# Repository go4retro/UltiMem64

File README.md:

# UltiMem64 

A 2 IC SRAM replacement for the Commodore 64 that offers all of the advantages of the VSP-fixed 64kB SRAM modules plus 2 megabytes of directly accessible RAM using a full featured memory management unit (MMU).

## Introduction

UltiMem64 replace the 2 4464 DRAM ICs on newer Commodore 64 motherboards (and can be installed in older 8-IC 4164 DRAM based motherboards using the DRAMCarrier PCB) and provides access to 2 megabytes of direct memory access (not REU access). The memory is instantly available when requested, no DMA needed.  The Color RAM IC installs in the 2114 space on motherboards containing a 2114 Color RAM and provides access to 64 kilobytes of Color memory nybbles.

## Technical Details

(*Although this information is currently correct, it may change based on developer feedback*)

The Commodore 64 64kB address space is partitioned into 16 4kB "pages", corresponding to the first nybble of a 16 bit address (the 'D' in $D0FF). The 2MB SRAM is likewise also partitioned into 4kB pages, which can then be mapped into any (or all) of the 16 slots in the MMU.

The MMU also supports the concept of a "mapping set", which means the developer can arrange up to 256 different 16 slot memory mappings, and choose any one of them at will.  Swapping out 64kB of RAM can take as little as 4 cycles (sta MAPPING_REG).

The system starts up in "hidden" mode, where the registers cannot be set or read from memory.  Reading some "magic addresses" will unhide the registers:

- $C0AA
- $C055
- $C0FF
- $C000
- $CO&lt;PAGE&gt;, where &lt;page&gt; is the high byte of the location where the registers should appear ($FF would place the registers at $ff00-)

Once the registers are visible, the are as follows:

| Register           | Bit  | Note                                       |
| ------------------ | ---- | ------------------------------------------ |
| BASE               | 0    | MMU enabled                                |
| BASE+1             | 7:0  | MMU mapping "window"                       |
| BASE+2             | 7:0  | MMU mapping in use                         |
| BASE+3             | 6:0  | Color RAM 1kB mapping                      |
| BASE+10 to BASE+1F | 7:0  | Low bits of 16 MMU mappings (16 mappings)  |
| BASE+20 to BASE+2F | 7:0  | High bits of 16 MMU mappings (16 mappings) |

To map memory, set the mapping "window" to the set you wish to change, and then alter the data in values BASE+10 to BASE+2F.  To run the code in that mapping, set the value of the map usage register to the desired map number (0-255).

Currently, to hide the registers, simply read the magic memory locations again and set the <page> to be 0.

The MMU replaces the upper 4 bits of the 16 bit memory address with the 9 bits of data from the mapping registers, using the upper 4 bits as a 0-15 "index" into the mapping set (mapping 0 will be used for memory access in the $0XXX range, etc.).  When the MMU is off, only the first 64kB of the SRAM is visible.

Since any mapping can point to any 4kB space in the real address space, one can place the same memory bank in multiple locations in the address map (map $123C00 so it appears at $4C00 and $FC00) or other interesting combinations.

The Color RAM mapping is simpler, and is simply a 6 bit value that choose which of the 64 1kB Color RAM "pages" will be used for the Color RAM data. There is no way to set Color RAM without switching to that specific mapping, so it is best to populate/change Color RAM during video blanking periods.

## Future Directions:

- Expand SRAM to 8MB (Alliance offers an 8MB SRAM in the same footprint)
- Utilize top two bits of MMU mapping to set read/write and IRQ on write flags for any 5kB page.
- Support a way to set mapping set without unhiding all registers (like 128 does)
- Possibly support a way to support auto-incremented memory store/read.

## License
Copyright (C) 2019-20  RETRO Innovations

These files are free designs; you can redistribute them and/or modify
them under the terms of the Creative Commons Attribution-ShareAlike 
4.0 International License.

You should have received a copy of the license along with this
work. If not, see <http://creativecommons.org/licenses/by-sa/4.0/>.

These files are distributed in the hope that they will be useful,
but WITHOUT ANY WARRANTY; without even the implied warranty of
MERCHANTABILITY or FITNESS FOR A PARTICULAR PURPOSE.  See the
license for more details.

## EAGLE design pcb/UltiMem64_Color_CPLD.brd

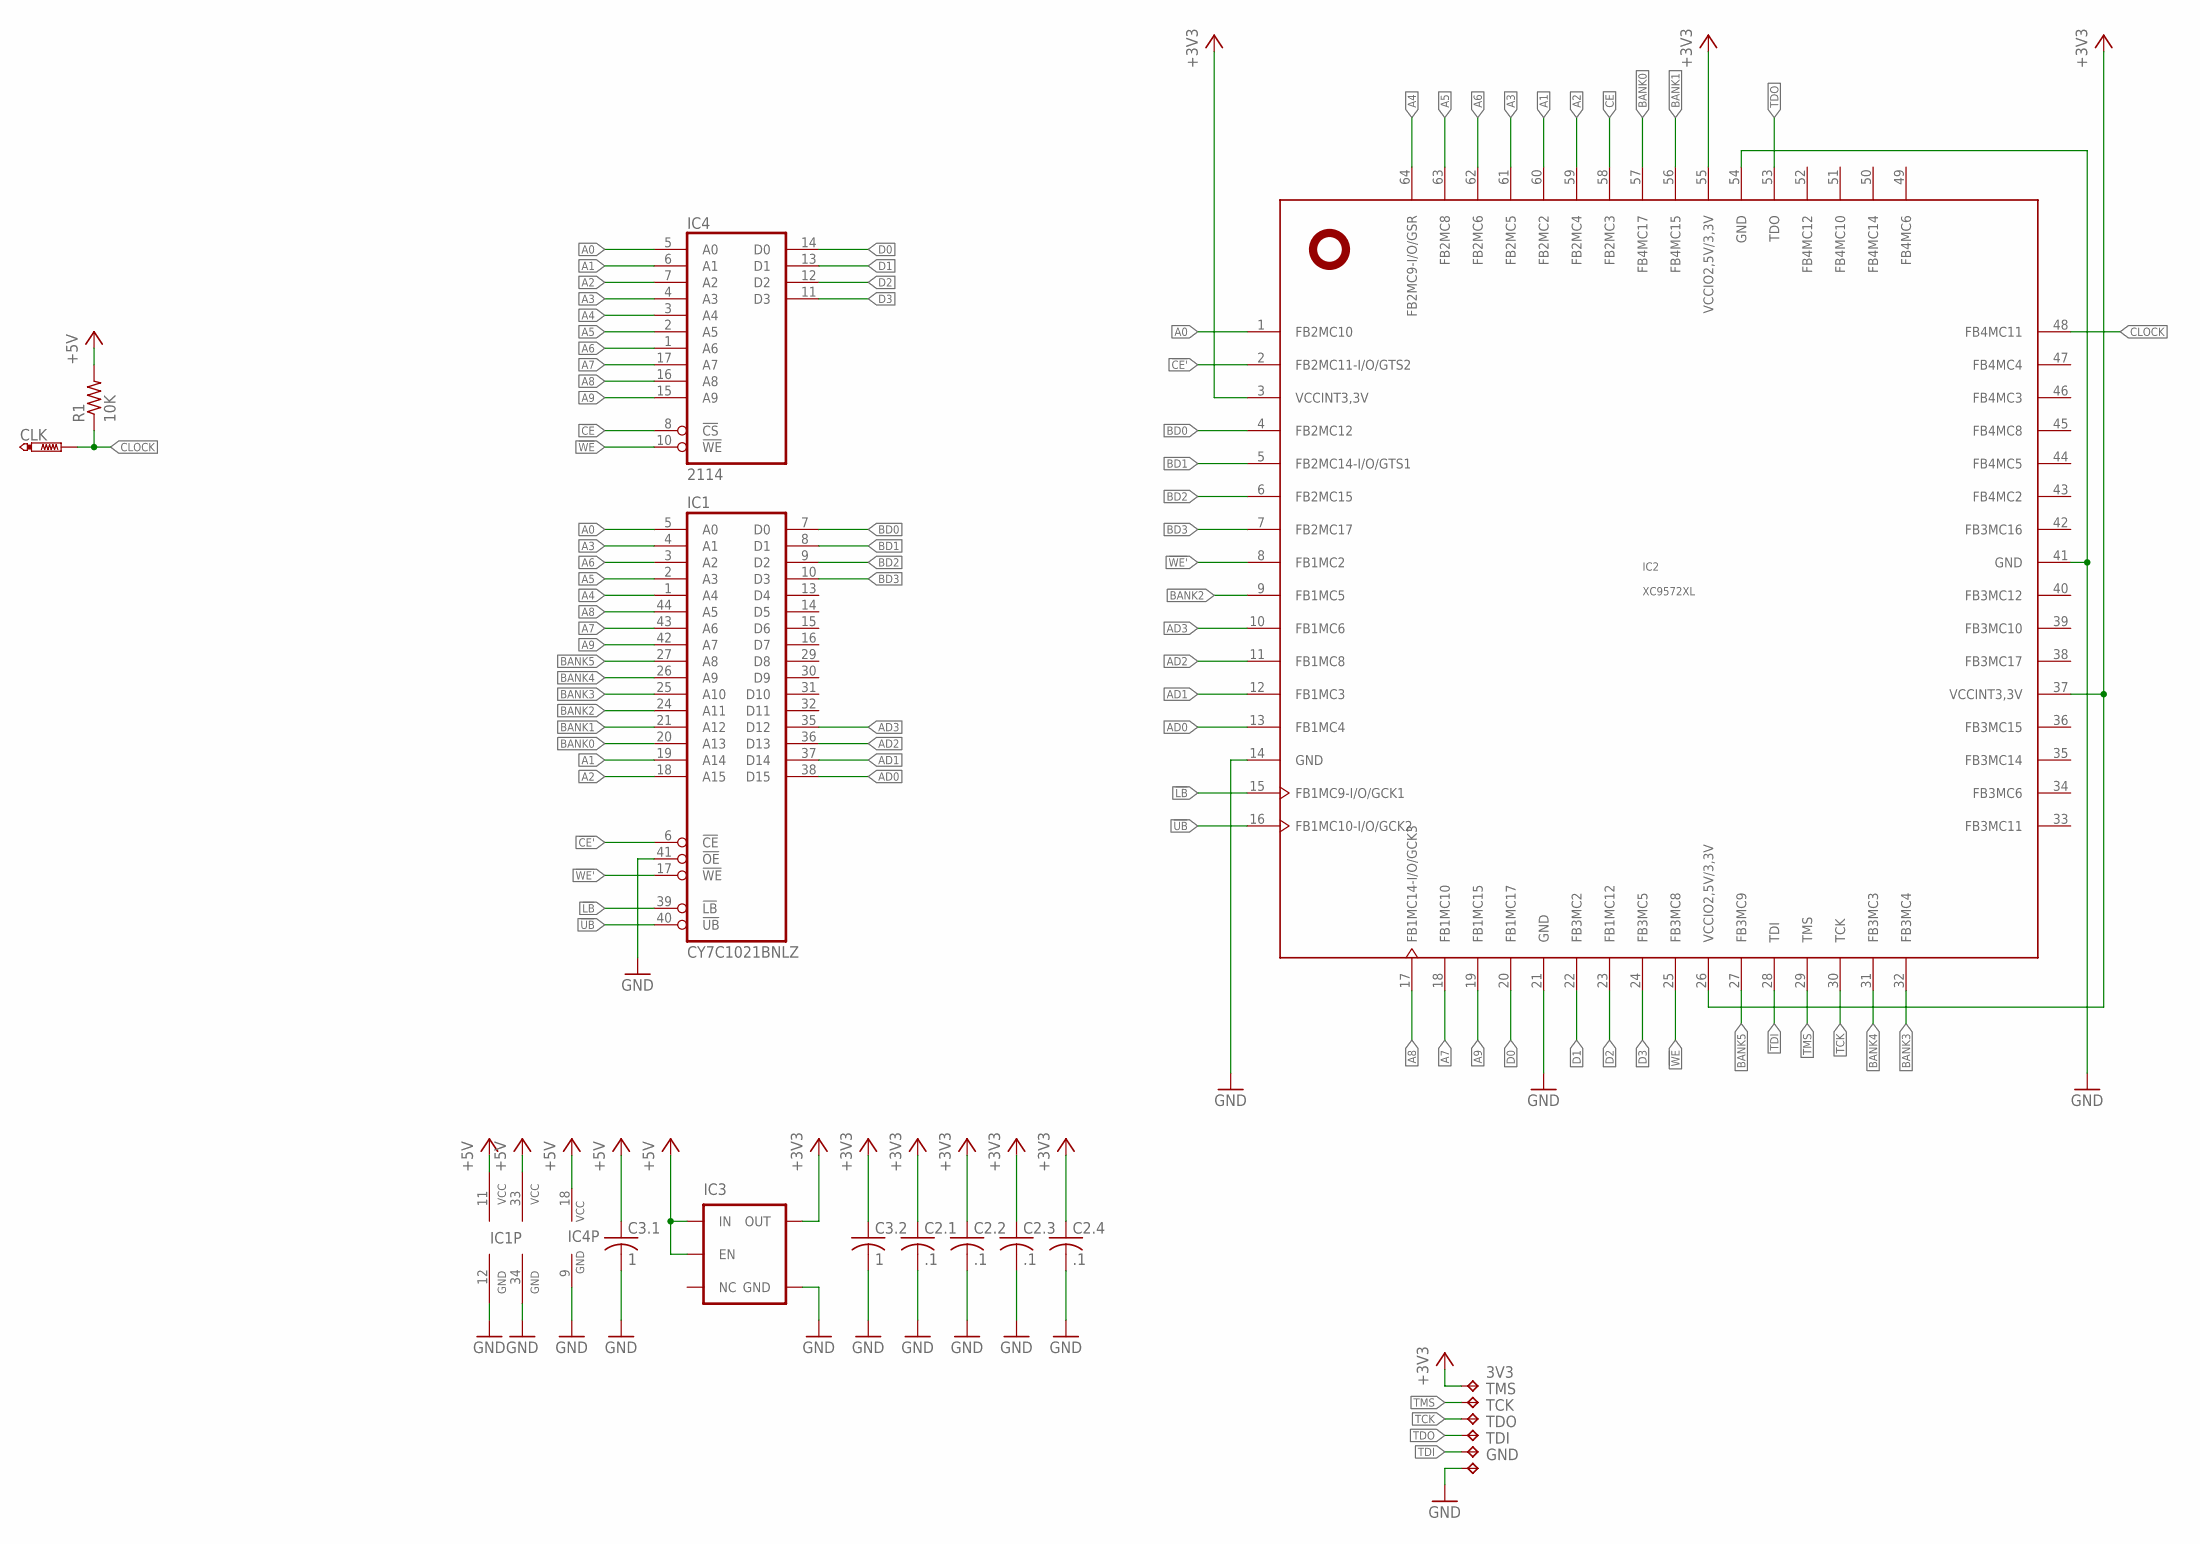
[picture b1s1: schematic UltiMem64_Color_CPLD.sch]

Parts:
3V3: TPTP09R; TP09R
C2.1, C2.2, C2.3, C2.4: .1; C0402
C3.1, C3.2: 1; C0402
CLK: PTR1PAD1-13; P1-13
GND: TPTP09R; TP09R
IC1: CY7C1021BNLZ; TSOP44-II
IC2: XC9572XL; VQFP64
IC3: V_REG_TPS76433SOT23-5; SOT23-5
IC4: 2114; DIL18-SMD-REVERSE
R1: 10K; R0402
TCK: TPTP09R; TP09R
TDI: TPTP09R; TP09R
TDO: TPTP09R; TP09R
TMS: TPTP09R; TP09R

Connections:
!CE: IC2.58 (FB2MC3), IC4.8 (!CS)
!CE': IC1.6 (!CE), IC2.2 (FB2MC11-I/O/GTS2)
!LB: IC1.39 (!LB), IC2.15 (FB1MC9-I/O/GCK1)
!UB: IC1.40 (!UB), IC2.16 (FB1MC10-I/O/GCK2)
!WE: IC2.25 (FB3MC8), IC4.10 (!WE)
!WE': IC1.17 (!WE), IC2.8 (FB1MC2)
+3V3: 3V3.TP, C2.1.1, C2.2.1, C2.3.1, C2.4.1, C3.2.1, IC2.3 (VCCINT3,3V), IC2.26 (VCCIO2,5V/3,3V), IC2.37 (VCCINT3,3V), IC2.55 (VCCIO2,5V/3,3V), IC3.5 (OUT)
+5V: C3.1.1, IC1.11 (VCC), IC1.33 (VCC), IC3.1 (IN), IC3.3 (EN), IC4.18 (VCC), R1.2
A0: IC1.5 (A0), IC2.1 (FB2MC10), IC4.5 (A0)
A1: IC1.19 (A14), IC2.60 (FB2MC2), IC4.6 (A1)
A2: IC1.18 (A15), IC2.59 (FB2MC4), IC4.7 (A2)
A3: IC1.4 (A1), IC2.61 (FB2MC5), IC4.4 (A3)
A4: IC1.1 (A4), IC2.64 (FB2MC9-I/O/GSR), IC4.3 (A4)
A5: IC1.2 (A3), IC2.63 (FB2MC8), IC4.2 (A5)
A6: IC1.3 (A2), IC2.62 (FB2MC6), IC4.1 (A6)
A7: IC1.43 (A6), IC2.18 (FB1MC10), IC4.17 (A7)
A8: IC1.44 (A5), IC2.17 (FB1MC14-I/O/GCK3), IC4.16 (A8)
A9: IC1.42 (A7), IC2.19 (FB1MC15), IC4.15 (A9)
AD0: IC1.38 (D15), IC2.13 (FB1MC4)
AD1: IC1.37 (D14), IC2.12 (FB1MC3)
AD2: IC1.36 (D13), IC2.11 (FB1MC8)
AD3: IC1.35 (D12), IC2.10 (FB1MC6)
BANK0: IC1.20 (A13), IC2.57 (FB4MC17)
BANK1: IC1.21 (A12), IC2.56 (FB4MC15)
BANK2: IC1.24 (A11), IC2.9 (FB1MC5)
BANK3: IC1.25 (A10), IC2.32 (FB3MC4)
BANK4: IC1.26 (A9), IC2.31 (FB3MC3)
BANK5: IC1.27 (A8), IC2.27 (FB3MC9)
BD0: IC1.7 (D0), IC2.4 (FB2MC12)
BD1: IC1.8 (D1), IC2.5 (FB2MC14-I/O/GTS1)
BD2: IC1.9 (D2), IC2.6 (FB2MC15)
BD3: IC1.10 (D3), IC2.7 (FB2MC17)
CLOCK: CLK.TP, IC2.48 (FB4MC11), R1.1
D0: IC2.20 (FB1MC17), IC4.14 (D0)
D1: IC2.22 (FB3MC2), IC4.13 (D1)
D2: IC2.23 (FB1MC12), IC4.12 (D2)
D3: IC2.24 (FB3MC5), IC4.11 (D3)
GND: C2.1.2, C2.2.2, C2.3.2, C2.4.2, C3.1.2, C3.2.2, GND.TP, IC1.12 (GND), IC1.34 (GND), IC1.41 (!OE), IC2.14 (GND), IC2.21 (GND), IC2.41 (GND), IC2.54 (GND), IC3.2 (GND), IC4.9 (GND)
TCK: IC2.30 (TCK), TCK.TP
TDI: IC2.28 (TDI), TDI.TP
TDO: IC2.53 (TDO), TDO.TP
TMS: IC2.29 (TMS), TMS.TP

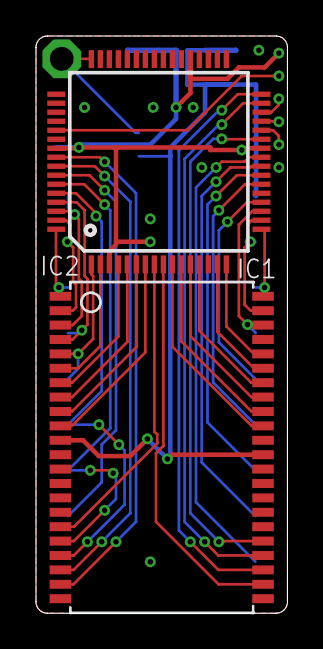
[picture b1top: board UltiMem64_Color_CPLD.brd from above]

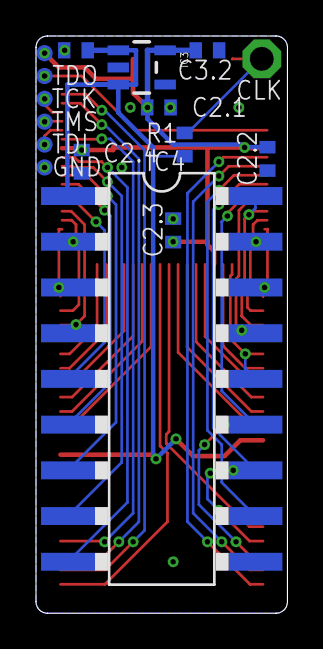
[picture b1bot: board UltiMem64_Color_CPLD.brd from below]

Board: 2 copper layers, 14.0 x 32.1 mm, 18 parts (15 on the bottom side), 42 nets.

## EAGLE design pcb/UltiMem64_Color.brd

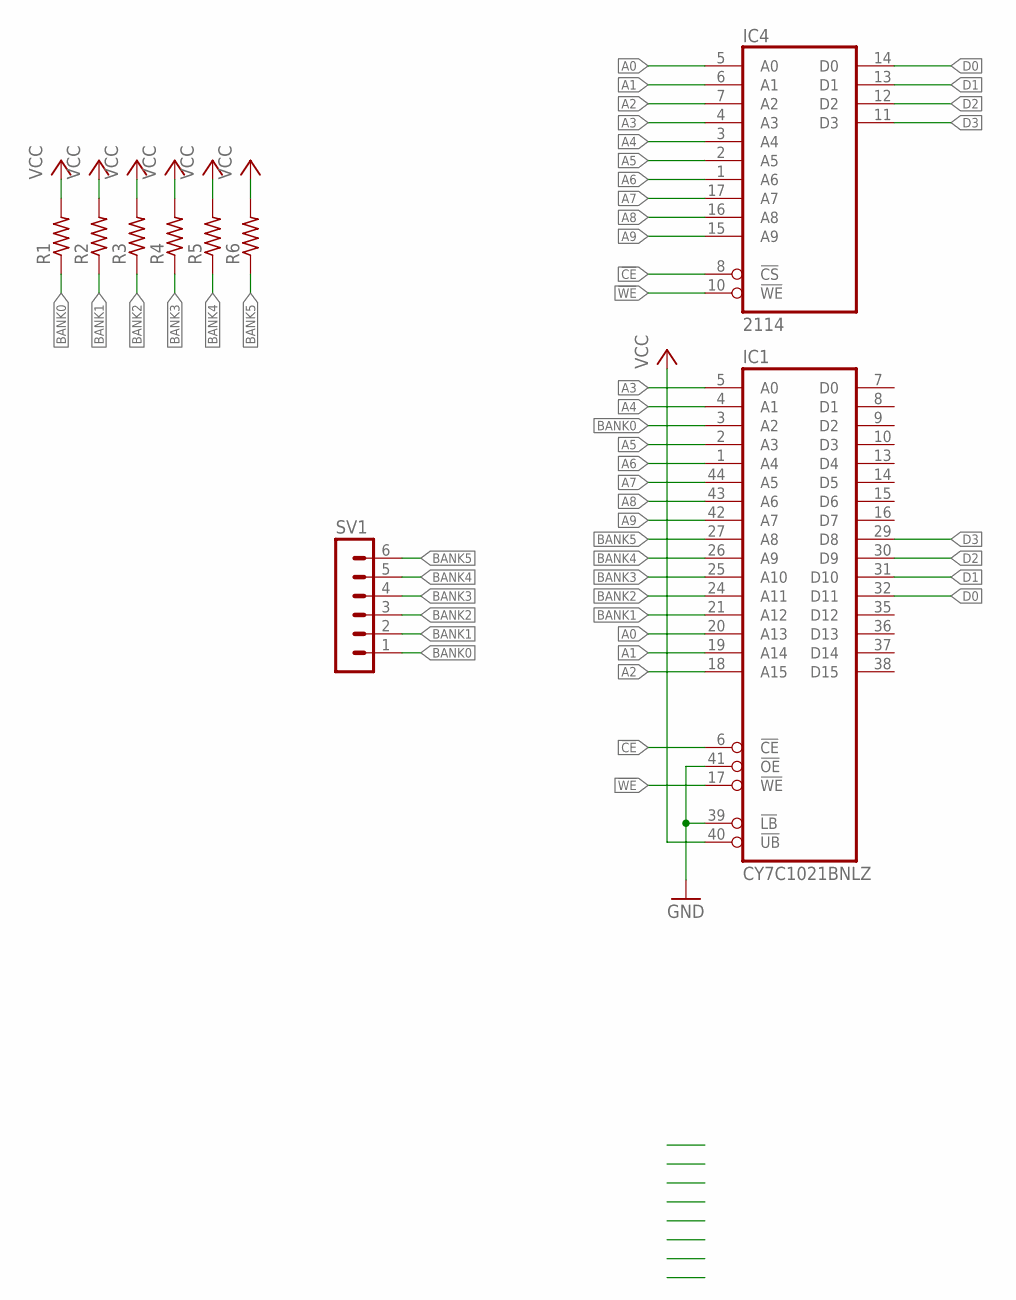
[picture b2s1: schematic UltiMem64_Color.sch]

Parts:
IC1: CY7C1021BNLZ; TSOP44-II
IC4: 2114; DIL18-SMD-REVERSE
R1, R2, R3, R4, R5, R6: R-US_R0402; R0402
SV1: MA06-1

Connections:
!CE: IC1.6 (!CE), IC4.8 (!CS)
!WE: IC1.17 (!WE), IC4.10 (!WE)
A0: IC1.20 (A13), IC4.5 (A0)
A1: IC1.19 (A14), IC4.6 (A1)
A2: IC1.18 (A15), IC4.7 (A2)
A3: IC1.5 (A0), IC4.4 (A3)
A4: IC1.4 (A1), IC4.3 (A4)
A5: IC1.2 (A3), IC4.2 (A5)
A6: IC1.1 (A4), IC4.1 (A6)
A7: IC1.44 (A5), IC4.17 (A7)
A8: IC1.43 (A6), IC4.16 (A8)
A9: IC1.42 (A7), IC4.15 (A9)
BANK0: IC1.3 (A2), R1.1, SV1.1
BANK1: IC1.21 (A12), R2.1, SV1.2
BANK2: IC1.24 (A11), R3.1, SV1.3
BANK3: IC1.25 (A10), R4.1, SV1.4
BANK4: IC1.26 (A9), R5.1, SV1.5
BANK5: IC1.27 (A8), R6.1, SV1.6
D0: IC1.32 (D11), IC4.14 (D0)
D1: IC1.31 (D10), IC4.13 (D1)
D2: IC1.30 (D9), IC4.12 (D2)
D3: IC1.29 (D8), IC4.11 (D3)
GND: IC1.12 (GND), IC1.34 (GND), IC1.39 (!LB), IC1.41 (!OE), IC4.9 (GND)
VCC: IC1.11 (VCC), IC1.33 (VCC), IC1.40 (!UB), IC4.18 (VCC), R1.2, R2.2, R3.2, R4.2, R5.2, R6.2

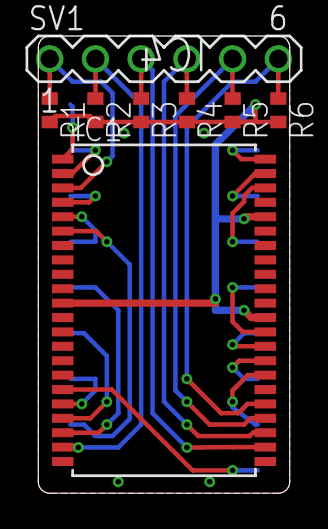
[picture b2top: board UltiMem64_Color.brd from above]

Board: 2 copper layers, 14.0 x 25.4 mm, 9 parts (0 on the bottom side), 24 nets.

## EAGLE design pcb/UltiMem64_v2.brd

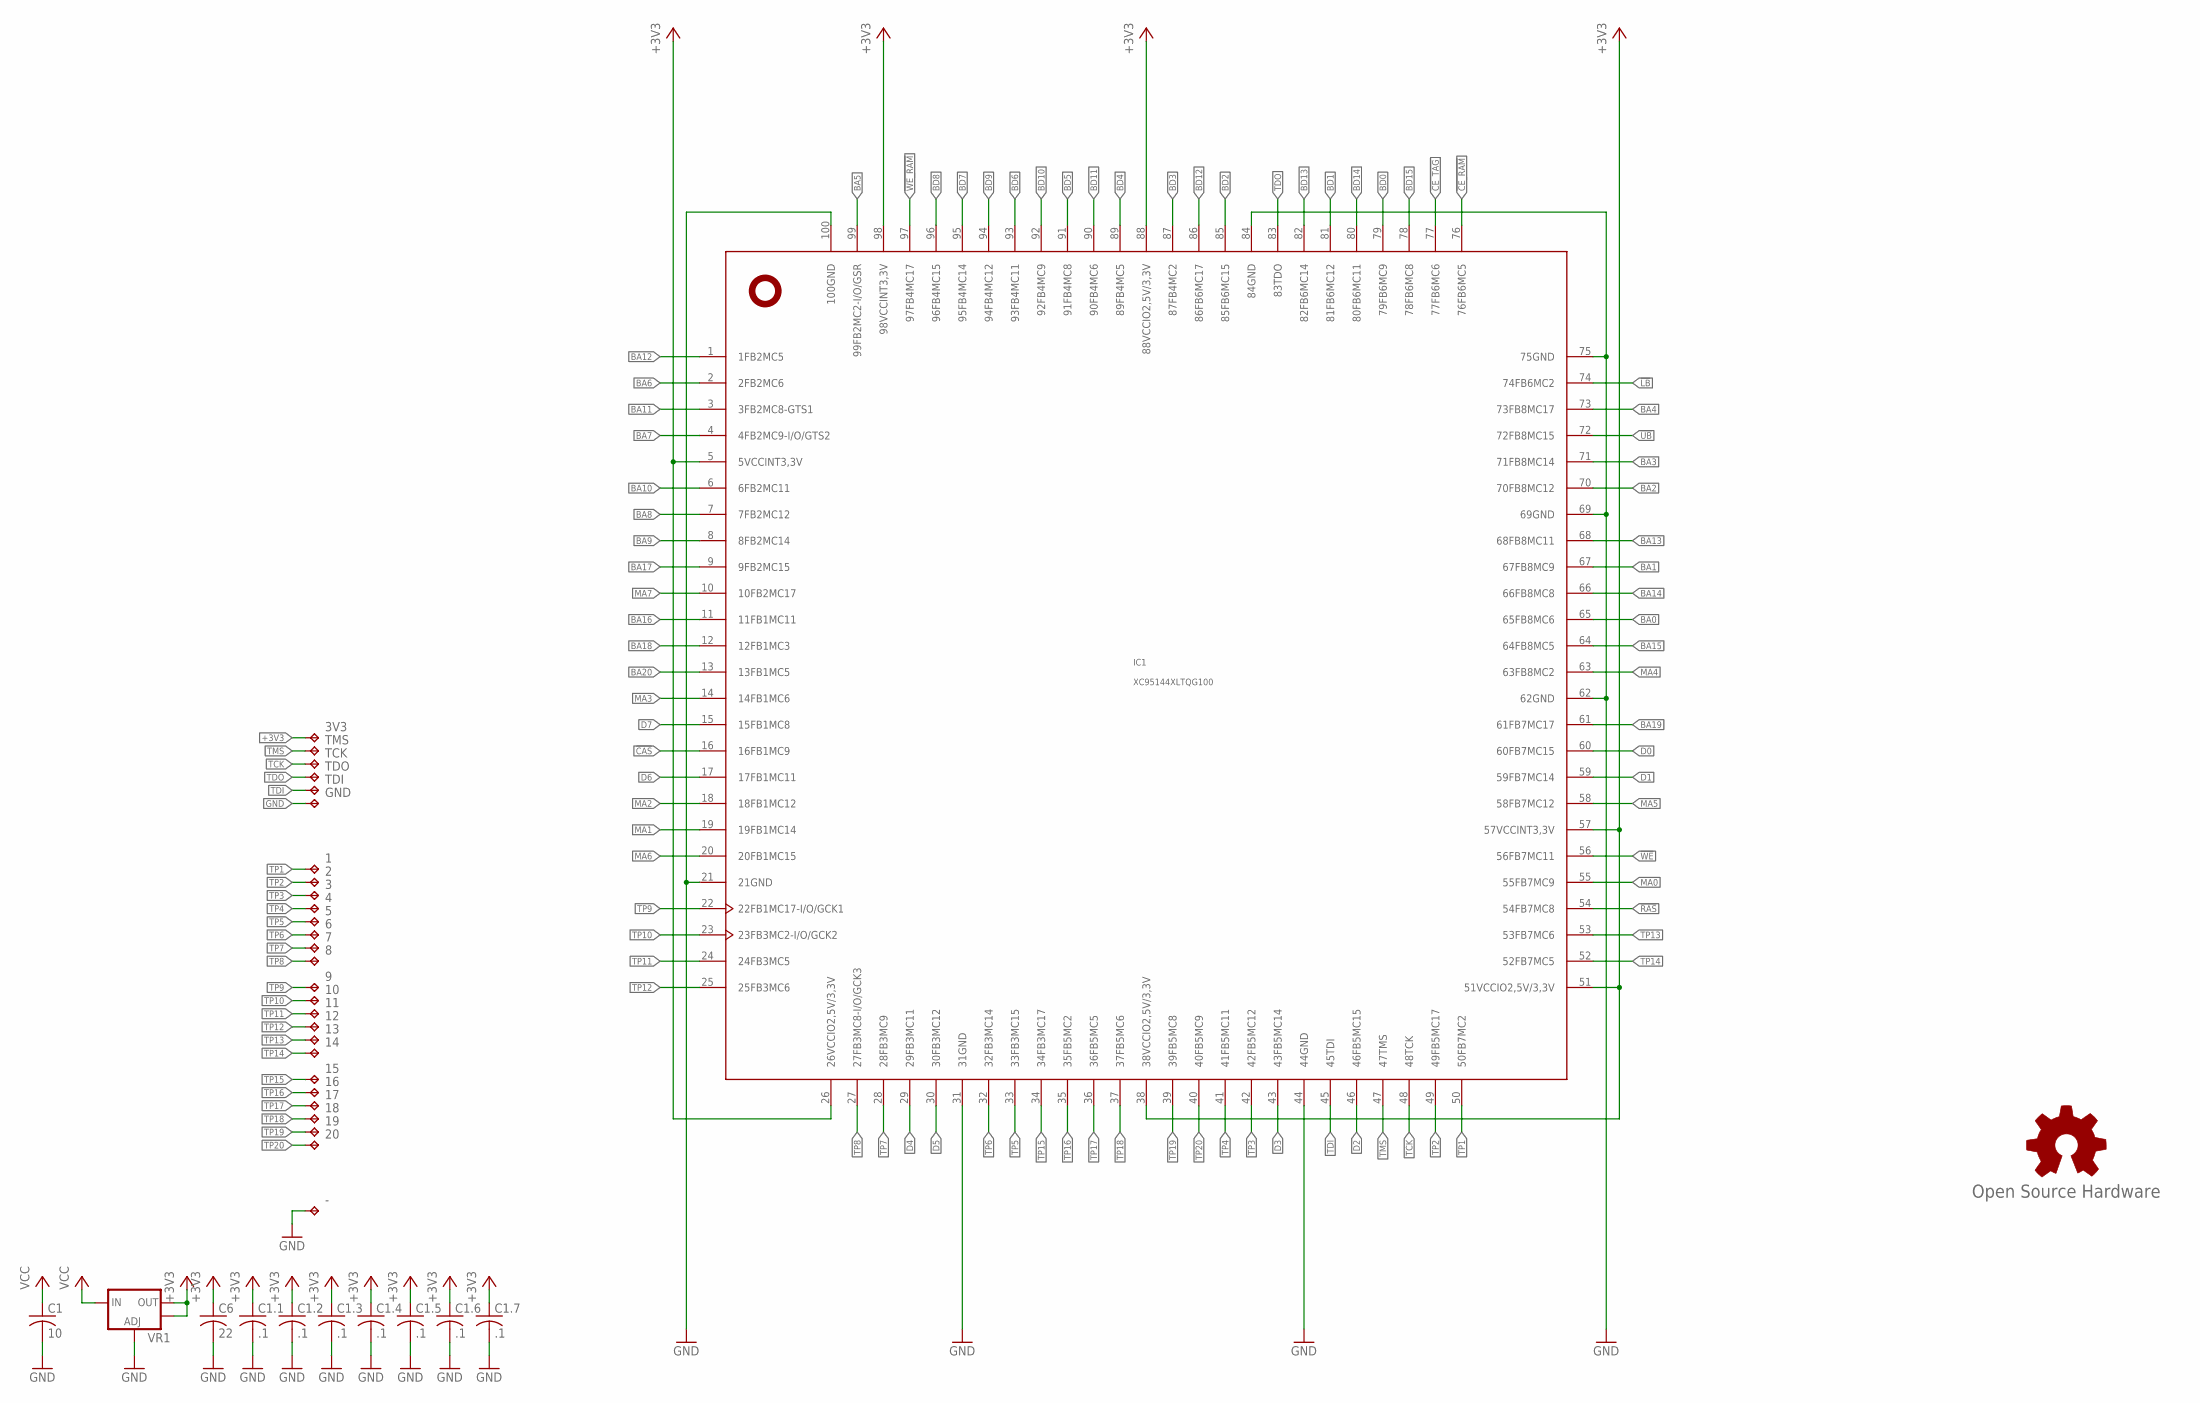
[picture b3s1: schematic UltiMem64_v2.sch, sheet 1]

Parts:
1, 2, 3, 4, 5, 6, 7, 8, 9, 10, 11, 12, 13, 14: TPPAD1-13; P1-13
3V3: TPTP09R; TP09R
15, 16, 17, 18, 19, 20: TPTP08R; TP08R
-: TPPAD1-13; P1-13
C1: 10; C0805
C1.1, C1.2, C1.3, C1.4, C1.5, C1.6, C1.7: .1; C0402
C6: 22; C0805
GND: TPTP10R; TP10R
GOLD_ORB_SM1: Open Source Hardware; OSHW_5MM
IC1: XC95144XLTQG100; TQFP100
TCK: TPTP09R; TP09R
TDI: TPTP09R; TP09R
TDO: TPTP09R; TP09R
TMS: TPTP09R; TP09R
VR1: V_REG_LM1117SOT223; SOT223

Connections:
!CAS: IC1.16 (16FB1MC9); also elsewhere on the board
!CE_RAM: IC1.76 (76FB6MC5); also elsewhere on the board
!CE_TAG: IC1.77 (77FB6MC6); also elsewhere on the board
!LB: IC1.74 (74FB6MC2); also elsewhere on the board
!RAS: IC1.54 (54FB7MC8); also elsewhere on the board
!UB: IC1.72 (72FB8MC15); also elsewhere on the board
!WE: IC1.56 (56FB7MC11); also elsewhere on the board
!WE_RAM: IC1.97 (97FB4MC17); also elsewhere on the board
+3V3: 3V3.TP, C1.1.1, C1.2.1, C1.3.1, C1.4.1, C1.5.1, C1.6.1, C1.7.1, C6.1, IC1.5 (5VCCINT3,3V), IC1.26 (26VCCIO2,5V/3,3V), IC1.38 (38VCCIO2,5V/3,3V), IC1.51 (51VCCIO2,5V/3,3V), IC1.57 (57VCCINT3,3V), IC1.88 (88VCCIO2,5V/3,3V), IC1.98 (98VCCINT3,3V), VR1.2 (OUT), VR1.4 (OUT); also elsewhere on the board
BA0: IC1.65 (65FB8MC6); also elsewhere on the board
BA1: IC1.67 (67FB8MC9); also elsewhere on the board
BA2: IC1.70 (70FB8MC12); also elsewhere on the board
BA3: IC1.71 (71FB8MC14); also elsewhere on the board
BA4: IC1.73 (73FB8MC17); also elsewhere on the board
BA5: IC1.99 (99FB2MC2-I/O/GSR); also elsewhere on the board
BA6: IC1.2 (2FB2MC6); also elsewhere on the board
BA7: IC1.4 (4FB2MC9-I/O/GTS2); also elsewhere on the board
BA8: IC1.7 (7FB2MC12); also elsewhere on the board
BA9: IC1.8 (8FB2MC14); also elsewhere on the board
BA10: IC1.6 (6FB2MC11); also elsewhere on the board
BA11: IC1.3 (3FB2MC8-GTS1); also elsewhere on the board
BA12: IC1.1 (1FB2MC5); also elsewhere on the board
BA13: IC1.68 (68FB8MC11); also elsewhere on the board
BA14: IC1.66 (66FB8MC8); also elsewhere on the board
BA15: IC1.64 (64FB8MC5); also elsewhere on the board
BA16: IC1.11 (11FB1MC11); also elsewhere on the board
BA17: IC1.9 (9FB2MC15); also elsewhere on the board
BA18: IC1.12 (12FB1MC3); also elsewhere on the board
BA19: IC1.61 (61FB7MC17); also elsewhere on the board
BA20: IC1.13 (13FB1MC5); also elsewhere on the board
BD0: IC1.79 (79FB6MC9); also elsewhere on the board
BD1: IC1.81 (81FB6MC12); also elsewhere on the board
BD2: IC1.85 (85FB6MC15); also elsewhere on the board
BD3: IC1.87 (87FB4MC2); also elsewhere on the board
BD4: IC1.89 (89FB4MC5); also elsewhere on the board
BD5: IC1.91 (91FB4MC8); also elsewhere on the board
BD6: IC1.93 (93FB4MC11); also elsewhere on the board
BD7: IC1.95 (95FB4MC14); also elsewhere on the board
BD8: IC1.96 (96FB4MC15); also elsewhere on the board
BD9: IC1.94 (94FB4MC12); also elsewhere on the board
BD10: IC1.92 (92FB4MC9); also elsewhere on the board
BD11: IC1.90 (90FB4MC6); also elsewhere on the board
BD12: IC1.86 (86FB6MC17); also elsewhere on the board
BD13: IC1.82 (82FB6MC14); also elsewhere on the board
BD14: IC1.80 (80FB6MC11); also elsewhere on the board
BD15: IC1.78 (78FB6MC8); also elsewhere on the board
D0: IC1.60 (60FB7MC15); also elsewhere on the board
D1: IC1.59 (59FB7MC14); also elsewhere on the board
D2: IC1.46 (46FB5MC15); also elsewhere on the board
D3: IC1.43 (43FB5MC14); also elsewhere on the board
D4: IC1.29 (29FB3MC11); also elsewhere on the board
D5: IC1.30 (30FB3MC12); also elsewhere on the board
D6: IC1.17 (17FB1MC11); also elsewhere on the board
D7: IC1.15 (15FB1MC8); also elsewhere on the board
GND: -.TP, C1.2, C1.1.2, C1.2.2, C1.3.2, C1.4.2, C1.5.2, C1.6.2, C1.7.2, C6.2, GND.TP, IC1.21 (21GND), IC1.31 (31GND), IC1.44 (44GND), IC1.62 (62GND), IC1.69 (69GND), IC1.75 (75GND), IC1.84 (84GND), IC1.100 (100GND), VR1.1 (ADJ); also elsewhere on the board
MA0: IC1.55 (55FB7MC9); also elsewhere on the board
MA1: IC1.19 (19FB1MC14); also elsewhere on the board
MA2: IC1.18 (18FB1MC12); also elsewhere on the board
MA3: IC1.14 (14FB1MC6); also elsewhere on the board
MA4: IC1.63 (63FB8MC2); also elsewhere on the board
MA5: IC1.58 (58FB7MC12); also elsewhere on the board
MA6: IC1.20 (20FB1MC15); also elsewhere on the board
MA7: IC1.10 (10FB2MC17); also elsewhere on the board
TCK: IC1.48 (48TCK), TCK.TP
TDI: IC1.45 (45TDI), TDI.TP
TDO: IC1.83 (83TDO), TDO.TP
TMS: IC1.47 (47TMS), TMS.TP
TP1: 1.TP, IC1.50 (50FB7MC2)
TP2: 2.TP, IC1.49 (49FB5MC17)
TP3: 3.TP, IC1.42 (42FB5MC12)
TP4: 4.TP, IC1.41 (41FB5MC11)
TP5: 5.TP, IC1.33 (33FB3MC15)
TP6: 6.TP, IC1.32 (32FB3MC14)
TP7: 7.TP, IC1.28 (28FB3MC9)
TP8: 8.TP, IC1.27 (27FB3MC8-I/O/GCK3)
TP9: 9.TP, IC1.22 (22FB1MC17-I/O/GCK1)
TP10: 10.TP, IC1.23 (23FB3MC2-I/O/GCK2)
TP11: 11.TP, IC1.24 (24FB3MC5)
TP12: 12.TP, IC1.25 (25FB3MC6)
TP13: 13.TP, IC1.53 (53FB7MC6)
TP14: 14.TP, IC1.52 (52FB7MC5)
TP15: 15.TP, IC1.34 (34FB3MC17)
TP16: 16.TP, IC1.35 (35FB5MC2)
TP17: 17.TP, IC1.36 (36FB5MC5)
TP18: 18.TP, IC1.37 (37FB5MC6)
TP19: 19.TP, IC1.39 (39FB5MC8)
TP20: 20.TP, IC1.40 (40FB5MC9)
VCC: C1.1, VR1.3 (IN); also elsewhere on the board

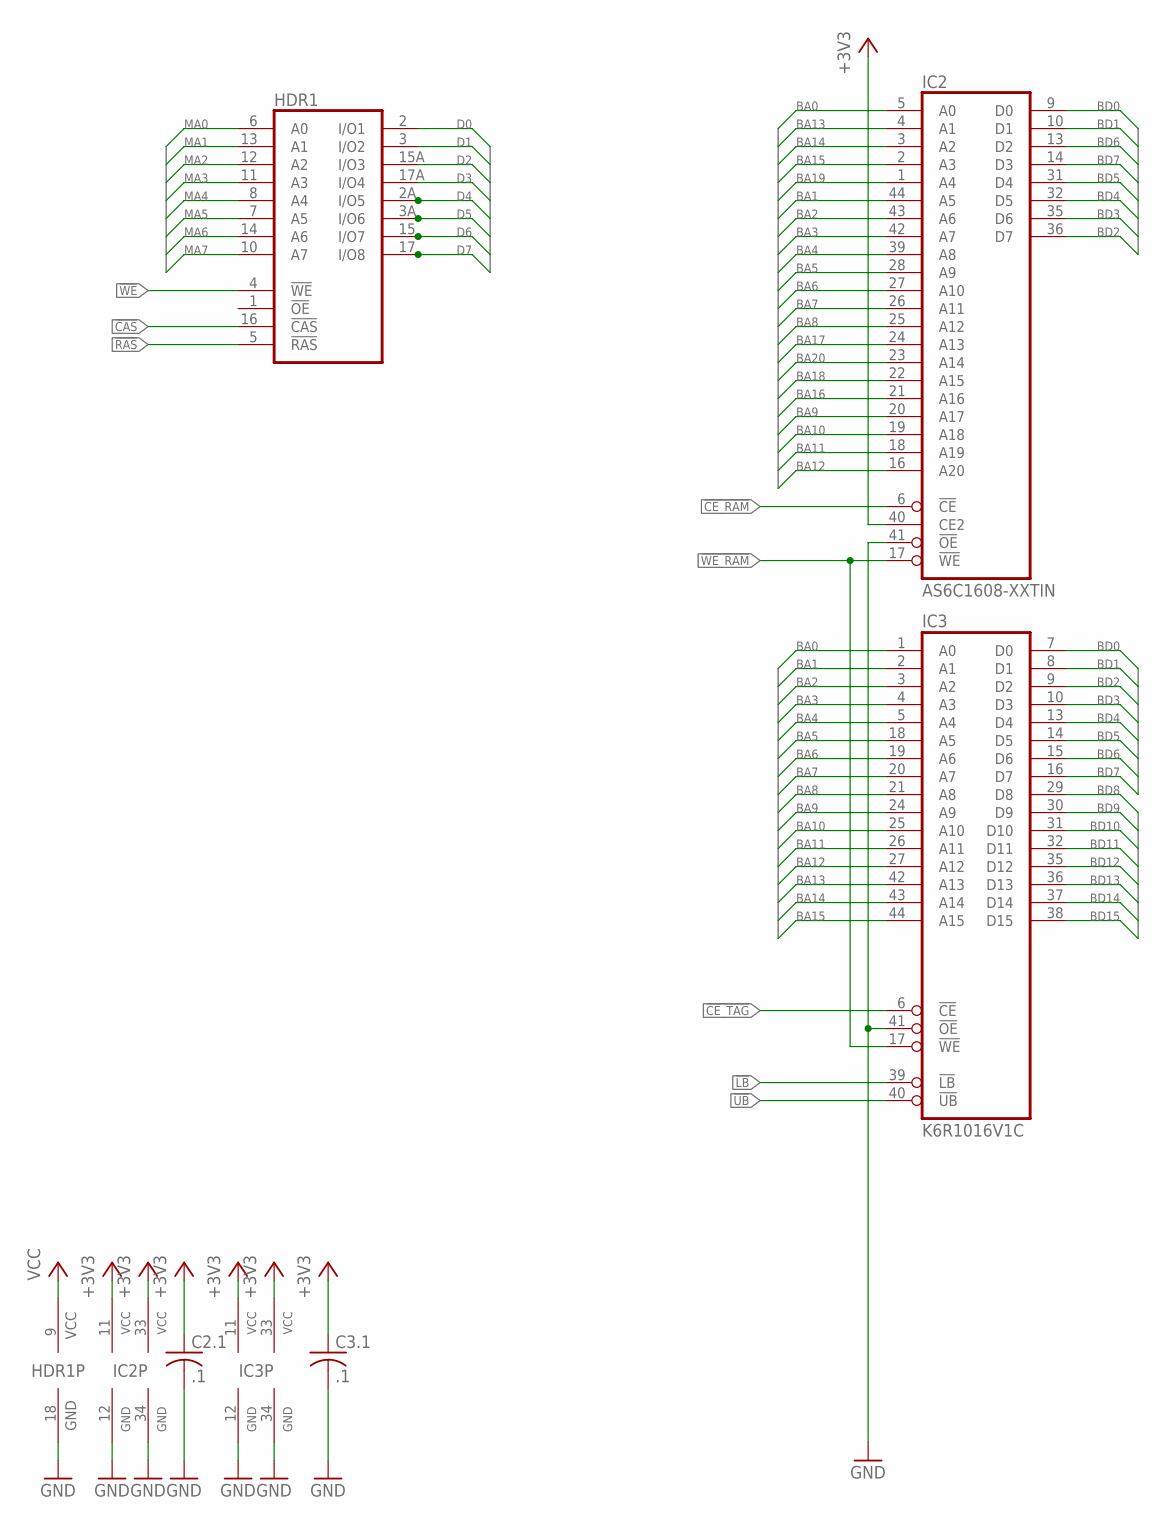
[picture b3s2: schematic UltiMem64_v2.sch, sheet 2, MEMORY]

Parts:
C2.1, C3.1: .1; C0402
HDR1: 2X41464C-HDR; 2XDIL18_REV
IC2: AS6C1608-XXTIN; TSOP44-II
IC3: K6R1016V1C; SOJ44/4

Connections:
!CAS: HDR1.16 (!CAS); also elsewhere on the board
!CE_RAM: IC2.6 (!CE); also elsewhere on the board
!CE_TAG: IC3.6 (!CE); also elsewhere on the board
!LB: IC3.39 (!LB); also elsewhere on the board
!RAS: HDR1.5 (!RAS); also elsewhere on the board
!UB: IC3.40 (!UB); also elsewhere on the board
!WE: HDR1.4 (!WE); also elsewhere on the board
!WE_RAM: IC2.17 (!WE), IC3.17 (!WE); also elsewhere on the board
+3V3: C2.1.1, C3.1.1, IC2.11 (VCC), IC2.33 (VCC), IC2.40 (CE2), IC3.11 (VCC), IC3.33 (VCC); also elsewhere on the board
BA0: IC2.5 (A0), IC3.1 (A0); also elsewhere on the board
BA1: IC2.44 (A5), IC3.2 (A1); also elsewhere on the board
BA2: IC2.43 (A6), IC3.3 (A2); also elsewhere on the board
BA3: IC2.42 (A7), IC3.4 (A3); also elsewhere on the board
BA4: IC2.39 (A8), IC3.5 (A4); also elsewhere on the board
BA5: IC2.28 (A9), IC3.18 (A5); also elsewhere on the board
BA6: IC2.27 (A10), IC3.19 (A6); also elsewhere on the board
BA7: IC2.26 (A11), IC3.20 (A7); also elsewhere on the board
BA8: IC2.25 (A12), IC3.21 (A8); also elsewhere on the board
BA9: IC2.20 (A17), IC3.24 (A9); also elsewhere on the board
BA10: IC2.19 (A18), IC3.25 (A10); also elsewhere on the board
BA11: IC2.18 (A19), IC3.26 (A11); also elsewhere on the board
BA12: IC2.16 (A20), IC3.27 (A12); also elsewhere on the board
BA13: IC2.4 (A1), IC3.42 (A13); also elsewhere on the board
BA14: IC2.3 (A2), IC3.43 (A14); also elsewhere on the board
BA15: IC2.2 (A3), IC3.44 (A15); also elsewhere on the board
BA16: IC2.21 (A16); also elsewhere on the board
BA17: IC2.24 (A13); also elsewhere on the board
BA18: IC2.22 (A15); also elsewhere on the board
BA19: IC2.1 (A4); also elsewhere on the board
BA20: IC2.23 (A14); also elsewhere on the board
BD0: IC2.9 (D0), IC3.7 (D0); also elsewhere on the board
BD1: IC2.10 (D1), IC3.8 (D1); also elsewhere on the board
BD2: IC2.36 (D7), IC3.9 (D2); also elsewhere on the board
BD3: IC2.35 (D6), IC3.10 (D3); also elsewhere on the board
BD4: IC2.32 (D5), IC3.13 (D4); also elsewhere on the board
BD5: IC2.31 (D4), IC3.14 (D5); also elsewhere on the board
BD6: IC2.13 (D2), IC3.15 (D6); also elsewhere on the board
BD7: IC2.14 (D3), IC3.16 (D7); also elsewhere on the board
BD8: IC3.29 (D8); also elsewhere on the board
BD9: IC3.30 (D9); also elsewhere on the board
BD10: IC3.31 (D10); also elsewhere on the board
BD11: IC3.32 (D11); also elsewhere on the board
BD12: IC3.35 (D12); also elsewhere on the board
BD13: IC3.36 (D13); also elsewhere on the board
BD14: IC3.37 (D14); also elsewhere on the board
BD15: IC3.38 (D15); also elsewhere on the board
D0: HDR1.2 (I/O1); also elsewhere on the board
D1: HDR1.3 (I/O2); also elsewhere on the board
D2: HDR1.15A (I/O3); also elsewhere on the board
D3: HDR1.17A (I/O4); also elsewhere on the board
D4: HDR1.2A (I/O5); also elsewhere on the board
D5: HDR1.3A (I/O6); also elsewhere on the board
D6: HDR1.15 (I/O7); also elsewhere on the board
D7: HDR1.17 (I/O8); also elsewhere on the board
GND: C2.1.2, C3.1.2, HDR1.18 (GND), IC2.12 (GND), IC2.34 (GND), IC2.41 (!OE), IC3.12 (GND), IC3.34 (GND), IC3.41 (!OE); also elsewhere on the board
MA0: HDR1.6 (A0); also elsewhere on the board
MA1: HDR1.13 (A1); also elsewhere on the board
MA2: HDR1.12 (A2); also elsewhere on the board
MA3: HDR1.11 (A3); also elsewhere on the board
MA4: HDR1.8 (A4); also elsewhere on the board
MA5: HDR1.7 (A5); also elsewhere on the board
MA6: HDR1.14 (A6); also elsewhere on the board
MA7: HDR1.10 (A7); also elsewhere on the board
VCC: HDR1.9 (VCC); also elsewhere on the board

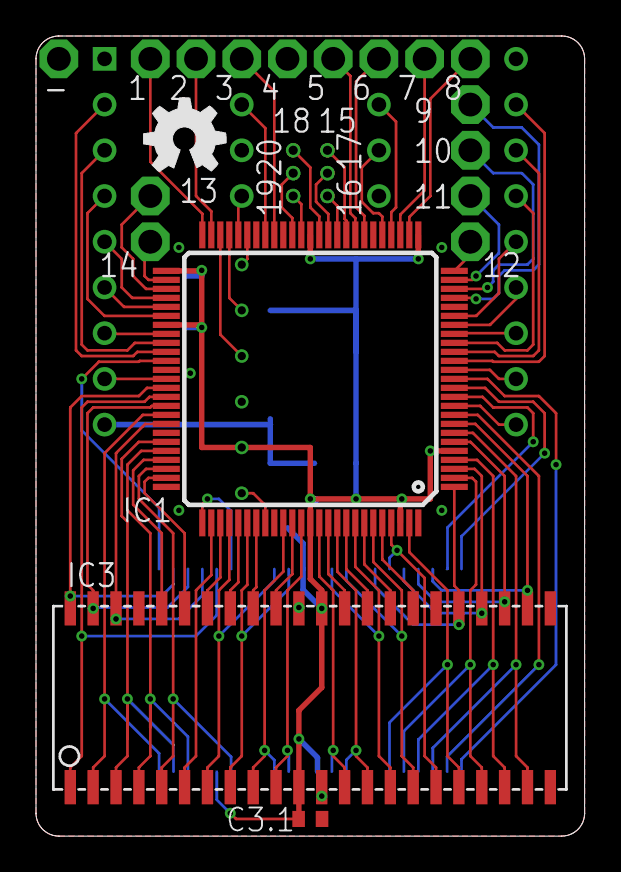
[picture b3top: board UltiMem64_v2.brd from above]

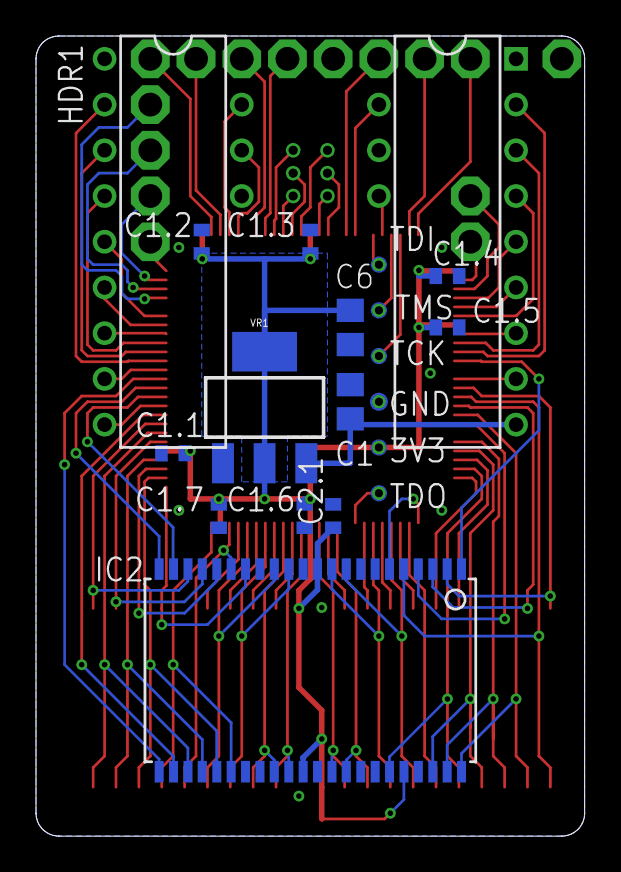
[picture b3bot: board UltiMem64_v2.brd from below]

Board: 2 copper layers, 30.5 x 44.5 mm, 44 parts (18 on the bottom side), 88 nets.

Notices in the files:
parts and their libraries:
SparkFun: Licensing: CC v3.0 Share-Alike You are welcome to use this library for commercial purposes.
